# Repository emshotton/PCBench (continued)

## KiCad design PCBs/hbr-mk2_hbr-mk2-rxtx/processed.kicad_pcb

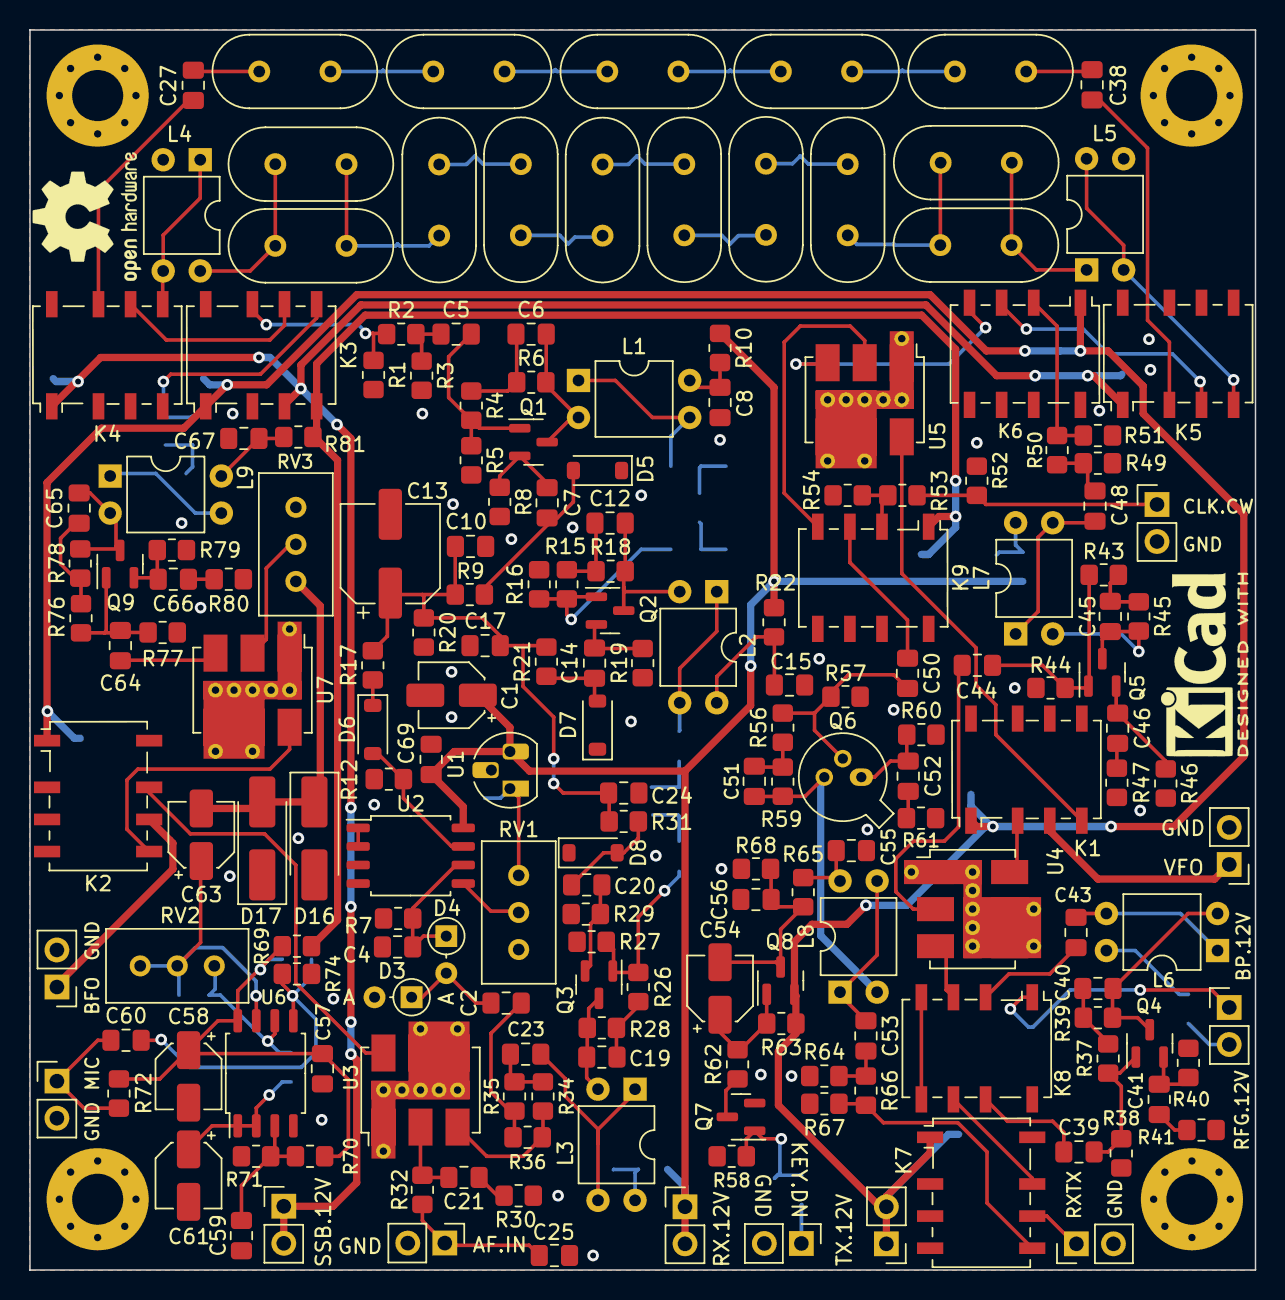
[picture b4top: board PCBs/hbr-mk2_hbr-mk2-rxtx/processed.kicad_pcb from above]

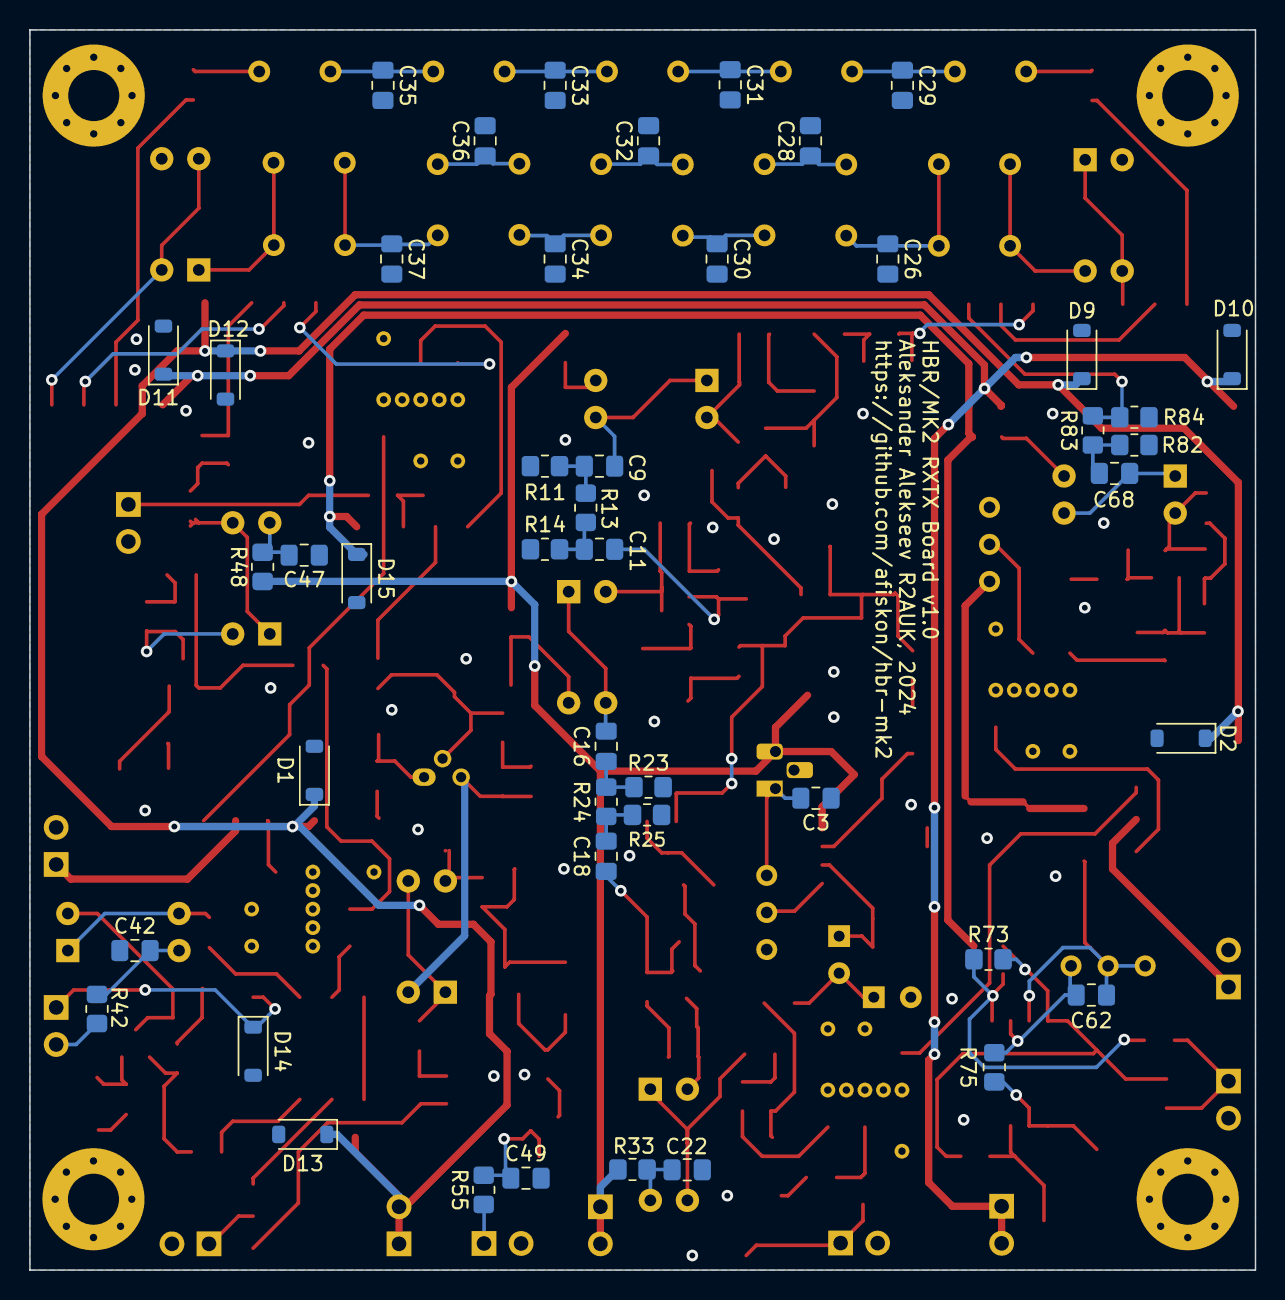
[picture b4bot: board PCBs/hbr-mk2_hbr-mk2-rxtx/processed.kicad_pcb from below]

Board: 2 copper layers, 84.0 x 85.0 mm, 239 parts (46 on the bottom side), 136 nets.

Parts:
C1, C58, C61, C63: 10u; CP_Elec_4x5.4
C2, C3, C5, C6, C7, C8, C9, C10, C11, C12, C14, C15, C16, C17, C18, C19, C20, C22, C23, C24, C39, C40, C41, C42, C43, C44, C45, C46, C47, C48, C49, C50, C51, C52, C53, C55, C56, C57, C59, C60, C64, C65, C66, C67, C68, C69: 0.1u; C_0805_2012Metric_Pad1.18x1.45mm_HandSolder
C4: 820p; C_0805_2012Metric_Pad1.18x1.45mm_HandSolder
C13: 100u; CP_Elec_6.3x7.7
C21: 10n; C_0805_2012Metric_Pad1.18x1.45mm_HandSolder
C25: 47n; C_0805_2012Metric_Pad1.18x1.45mm_HandSolder
C26, C28, C30, C32, C34, C36, C37: 56p; C_0805_2012Metric_Pad1.18x1.45mm_HandSolder
C27, C29, C31, C33, C35, C38: 270p; C_0805_2012Metric_Pad1.18x1.45mm_HandSolder
C54: 2.2u; CP_Elec_4x5.4
C62: 1n; C_0805_2012Metric_Pad1.18x1.45mm_HandSolder
D1, D2, D5, D6, D7, D8, D9, D10, D11, D12, D13, D14, D15: 1N4148W; D_SOD-123
D3, D4: 1N34/D311; D_DO-34_SOD68_P2.54mm_Vertical_AnodeUp
D16, D17: SS14; D_SMA_Handsoldering
H1, H2, H3, H4: MountingHole_Pad; MountingHole_3.5mm_Pad_Via
J1, J2, J3, J4, J5, J6, J7, J8, J9, J10, J11: Conn_01x02; PinHeader_1x02_P2.54mm_Vertical
K1, K2, K3, K4, K5, K6, K7, K8, K9: G6K-2F-Y; Relay_DPDT_Omron_G6K-2F-Y
L1, L2, L3, L4, L5, L6, L7, L8, L9: FT37-43; DIP-4_W7.62mm
Q1, Q2, Q3, Q4, Q5, Q9: MMBT3904; SOT-23
Q6: KT3142A; TO-18-3
Q7: 2N7002; SOT-23
Q8: MMBT3906; SOT-23
R1, R3, R11, R14, R23, R25, R49, R51, R64, R67, R82, R84: 150; R_0805_2012Metric_Pad1.20x1.40mm_HandSolder
R2, R13, R24, R50, R66, R83: 36; R_0805_2012Metric_Pad1.20x1.40mm_HandSolder
R4, R15, R26: 820; R_0805_2012Metric_Pad1.20x1.40mm_HandSolder
R5, R9, R16, R20, R21, R27, R31, R38, R44, R57, R72, R75, R77: 1K; R_0805_2012Metric_Pad1.20x1.40mm_HandSolder
R6, R18, R28, R39, R45, R59, R78: 3.3K; R_0805_2012Metric_Pad1.20x1.40mm_HandSolder
R7, R12, R58, R70, R71, R73, R74: 10K; R_0805_2012Metric_Pad1.20x1.40mm_HandSolder
R8, R19, R29, R40, R46, R60, R79: 68; R_0805_2012Metric_Pad1.20x1.40mm_HandSolder
R10, R22, R33: 100; R_0805_2012Metric_Pad1.20x1.40mm_HandSolder
R17: 220; R_0805_2012Metric_Pad1.20x1.40mm_HandSolder
R30, R34, R35, R36: 51; R_0805_2012Metric_Pad1.20x1.40mm_HandSolder
R32: 1.5K; R_0805_2012Metric_Pad1.20x1.40mm_HandSolder
R37, R43, R56, R76: 1.3K; R_0805_2012Metric_Pad1.20x1.40mm_HandSolder
R41, R47, R61, R80: 6; R_0805_2012Metric_Pad1.20x1.40mm_HandSolder
R42, R48, R55, R65, R69, R81: 22; R_0805_2012Metric_Pad1.20x1.40mm_HandSolder
R52, R53, R54: 82; R_0805_2012Metric_Pad1.20x1.40mm_HandSolder
R62: 2.2K; R_0805_2012Metric_Pad1.20x1.40mm_HandSolder
R63: 680; R_0805_2012Metric_Pad1.20x1.40mm_HandSolder
R68: 1.8K; R_0805_2012Metric_Pad1.20x1.40mm_HandSolder
RV1, RV3: 10K; Potentiometer_Bourns_3296W_Vertical
RV2: 100K; Potentiometer_Bourns_3296W_Vertical
SYM1: Logo_Open_Hardware_Small; OSHW-Logo2_9.8x8mm_SilkScreen
SYM2: SYM_Radio_Waves_Large; KiCad-Logo2_5mm_SilkScreen
U1: L78L33; TO-92_HandSolder
U2: LM358; SOIC-8_5.23x5.23mm_P1.27mm
U3, U4, U5, U7: ADE-6; Mini-Circuits_CD542_LandPatternPL-052
U6: NE5532; SOIC-8_5.23x5.23mm_P1.27mm
Y1, Y2, Y3, Y4, Y5, Y6, Y7, Y8, Y9, Y10, Y11, Y12, Y13, Y14, Y15: 9.000; Crystal_HC49-U_Vertical

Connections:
AGC_DET: C2.1, R35.2, R36.2
AGC_OUT: R34.2, R36.1, U3.3 (RF)
AGC_VC: C10.2, C13.1, C17.2, C24.2, R9.2, R17.2, R20.1, R21.2, R31.2
BFO_RX: K2.7, U3.6 (LO)
BFO_TX: K2.5, U7.6 (LO)
GND: C1.2, C3.1, C4.1, C8.1, C10.1, C13.2, C15.1, C17.1, C22.1, C24.1, C25.1, C26.2, C28.2, C29.2, C30.2, C31.2, C32.2, C33.2, C34.2, C35.2, C36.2, C37.2, C42.1, C47.1, C49.2, C55.2, C56.2, C57.2, C58.2, C59.2, C61.2, C67.1, C69.1, D1.2 (A), D2.2 (A), D3.2 (A), D5.1 (K), D7.1 (K), D8.1 (K), D9.2 (A), D10.2 (A), D11.2 (A), D12.2 (A), D13.2 (A), D14.2 (A), D15.2 (A), D16.2 (A), D17.1 (K), H1.1, H2.1, H3.1, H4.1, J4.2, J5.2, J6.2, J7.2, J9.2, J10.2, J11.2, K1.5, K1.6, K1.7, K1.8, K2.2, K2.3, K2.4, K2.8, K3.8, K4.2, K4.3, K4.4, K4.8, K5.5, K5.6, K5.7, K5.8, K6.5, K6.6, K6.7, K6.8, K7.2, K7.3, K7.4, K7.8, K8.8, K9.5, K9.6, K9.7, K9.8, L4.2, L5.3, Q7.2 (S), R1.2, R3.2, R5.2, R7.2, R8.2, R11.2, R12.2, R14.2, R16.2, R19.2, R20.2, R23.2, R25.2, R27.2, R29.2, R30.2, R38.2, R40.2, R41.2, R44.2, R46.2, R47.2, R49.2, R51.2, R52.2, R54.2, R57.2, R58.2, R60.2, R61.2, R64.2, R67.2, R68.2, R71.2, R74.2, R77.2, R79.2, R80.2, R82.2, R84.2, RV1.3, RV3.3, U1.2 (GND), U2.3 (+), U2.4 (V-), U3.1 (GND), U3.4 (GND), U3.5 (GND), U4.1 (GND), U4.4 (GND), U4.5 (GND), U5.1 (GND), U5.4 (GND), U5.5 (GND), U6.4 (V-), U7.1 (GND), U7.4 (GND), U7.5 (GND)
unnamed: C5.1, R2.2, R3.1
unnamed: C6.1, R4.1, R6.1
unnamed: C8.2, L1.4, R10.2
unnamed: C9.1, L1.1, L1.3
unnamed: C9.2, R11.1, R13.1
unnamed: C11.1, R13.2, R14.1
unnamed: C12.1, R15.1, R18.1
unnamed: C15.2, L2.4, R22.2
unnamed: C16.1, L2.1, L2.3
unnamed: C16.2, R23.1, R24.1
unnamed: C18.1, R24.2, R25.1
unnamed: C19.1, R26.1, R28.1
unnamed: C21.1, R30.1
unnamed: C22.2, L3.4, R33.2
unnamed: C23.1, L3.1, L3.3
unnamed: C23.2, R34.1, R35.1
unnamed: C26.1, Y1.2, Y2.2, Y3.1
unnamed: C27.1, K4.7
unnamed: C27.2, Y4.1
unnamed: C28.1, Y3.2, Y5.1
unnamed: C29.1, Y4.2, Y6.1
unnamed: C30.1, Y5.2, Y7.1
unnamed: C31.1, Y6.2, Y8.2
unnamed: C32.1, Y7.2, Y9.2
unnamed: C33.1, Y8.1, Y10.2
unnamed: C34.1, Y9.1, Y11.2
unnamed: C35.1, Y10.1, Y12.2
unnamed: C36.1, Y11.1, Y13.2
unnamed: C37.1, Y13.1, Y14.2, Y15.2
unnamed: C38.1, Y12.1
unnamed: C38.2, K5.2
unnamed: C39.1, K8.7
unnamed: C40.1, R37.1, R39.1
unnamed: C41.1, R41.1
unnamed: C42.2, L6.4, R42.2
unnamed: C43.1, L6.1, L6.3
unnamed: C43.2, K8.2
unnamed: C45.1, R43.1, R45.1
unnamed: C46.1, R47.1
unnamed: C47.2, L7.4, R48.2
unnamed: C48.1, L7.1, L7.3
unnamed: C48.2, R49.1, R50.1
unnamed: C50.1, K9.3
unnamed: C51.1, R56.1, R59.1
unnamed: C52.1, R61.1
unnamed: C53.1, L8.1, L8.3
unnamed: C53.2, R64.1, R66.1
unnamed: C55.1, L8.4, R65.2
unnamed: C62.2, C63.1, RV2.1, RV2.2, U6.7
unnamed: C65.1, R76.1, R78.1
unnamed: C66.1, R80.1
unnamed: C67.2, L9.4, R81.2
unnamed: C68.1, L9.1, L9.3
unnamed: C68.2, R82.1, R83.1
unnamed: C2.2, D3.1 (K), D4.2 (A)
unnamed: C4.2, D4.1 (K), R7.1, U2.6 (-)
unnamed: C7.1, D5.2 (A), R9.1
unnamed: D6.2 (A), R12.1, U2.7
unnamed: D6.1 (K), R17.1
unnamed: C14.1, D7.2 (A), R21.1
unnamed: C20.1, D8.2 (A), R31.1
unnamed: C63.2, D16.1 (K), D17.2 (A), RV3.1
unnamed: J4.1, K1.3
unnamed: J5.1, K2.6
unnamed: C25.2, J6.1, R32.2
unnamed: J7.1, K7.6
unnamed: J9.1, R52.1, R53.1
unnamed: J10.1, R55.1
unnamed: C60.1, J11.1, R72.2
unnamed: K3.6, K4.6
unnamed: K4.5, L4.1, L4.3
unnamed: K5.3, K6.3
unnamed: K5.4, L5.2, L5.4
unnamed: K7.7, K8.6
unnamed: K9.2, R53.2, R54.1
unnamed: L4.4, Y1.1, Y2.1
unnamed: L5.1, Y14.1, Y15.1
unnamed: C5.2, Q1.1 (B), R4.2, R5.1
unnamed: C6.2, L1.2, Q1.3 (C), R6.2
unnamed: C7.2, Q1.2 (E), R8.1
unnamed: C11.2, Q2.1 (B), R15.2, R16.1
unnamed: C12.2, L2.2, Q2.3 (C), R18.2
unnamed: C14.2, Q2.2 (E), R19.1
unnamed: C18.2, Q3.1 (B), R26.2, R27.1
unnamed: C19.2, L3.2, Q3.3 (C), R28.2
unnamed: C20.2, Q3.2 (E), R29.1
unnamed: C39.2, Q4.1 (B), R37.2, R38.1
unnamed: C40.2, L6.2, Q4.3 (C), R39.2
unnamed: C41.2, Q4.2 (E), R40.1
unnamed: C44.2, Q5.1 (B), R43.2, R44.1
unnamed: C45.2, L7.2, Q5.3 (C), R45.2
unnamed: C46.2, Q5.2 (E), R46.1
unnamed: C50.2, Q6.2 (B), R56.2, R57.1
unnamed: C51.2, L8.2, Q6.3 (C), R59.2
unnamed: C52.2, Q6.1 (E), R60.1
unnamed: Q7.3 (D), R62.1
unnamed: C49.1, Q7.1 (G), R55.2, R58.1
unnamed: C54.1, Q8.1 (B), R62.2, R63.2
unnamed: C54.2, C56.1, Q8.3 (C), R65.1, R68.1
unnamed: C64.2, Q9.1 (B), R76.2, R77.1
unnamed: C65.2, L9.2, Q9.3 (C), R78.2
unnamed: C66.2, Q9.2 (E), R79.1
unnamed: C3.2, RV1.1, U1.1 (VO)
unnamed: U2.1, U2.2 (-)
unnamed: RV1.2, U2.5 (+)
unnamed: C21.2, R32.1, U3.2 (IF)
unnamed: C44.1, U4.2 (IF)
unnamed: K8.3, U4.3 (RF)
unnamed: K9.4, U5.2 (IF)
unnamed: C59.1, R70.2, R71.1, U6.3 (+)
unnamed: C61.1, R75.2, U6.1, U6.2 (-)
unnamed: C60.2, R73.2, R74.1, U6.5 (+)
unnamed: C62.1, R75.1, RV2.3, U6.6 (-)
unnamed: C57.1, C58.1, R69.2, R70.1, R72.1, R73.1, U6.8 (V+)
unnamed: RV3.2, U7.2 (IF)
unnamed: C64.1, U7.3 (RF)
RF_AMP_12V: J8.2, R42.1
RF_AMP_BYPASS: K8.4, K8.5
RF_AMP_BYPASS_12V: D14.1 (K), J8.1, K8.1
RX_12V: C1.1, C69.2, J1.1, J1.2, R10.1, R22.1, R33.1, R48.1, U1.3 (VI), U2.8 (V+)
SSB_12V: D10.1 (K), D11.1 (K), J3.1, J3.2, K3.3, K4.1, K5.1
SSB_TX_12V: D15.1 (K), K3.4, K9.1, R69.1, R81.1
TX_12V: D1.1 (K), D2.1 (K), D9.1 (K), D12.1 (K), D13.1 (K), J2.1, J2.2, K1.1, K2.1, K3.1, K6.1, K7.1, Q8.2 (E), R63.1
TX_COMMON_OUT: K7.5, R66.2, R67.1
VFO_RX: K1.2, U4.6 (LO)
VFO_TX: K1.4, U5.6 (LO)
XFLT_RX_IN: K6.2, R50.2, R51.1
XFLT_RX_OUT: K3.7, R1.1, R2.1
XFLT_TX_IN: K3.5, R83.2, R84.1
XFLT_TX_OUT: K6.4, U5.3 (RF)

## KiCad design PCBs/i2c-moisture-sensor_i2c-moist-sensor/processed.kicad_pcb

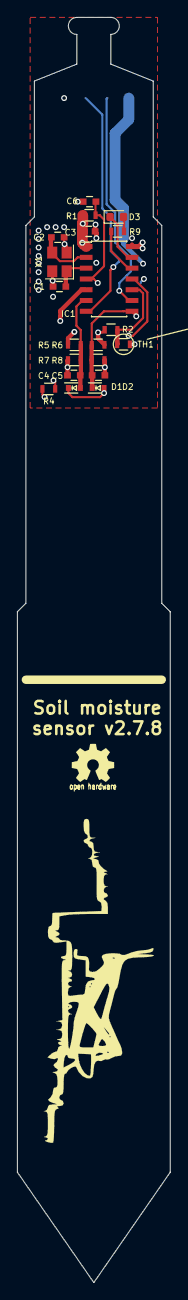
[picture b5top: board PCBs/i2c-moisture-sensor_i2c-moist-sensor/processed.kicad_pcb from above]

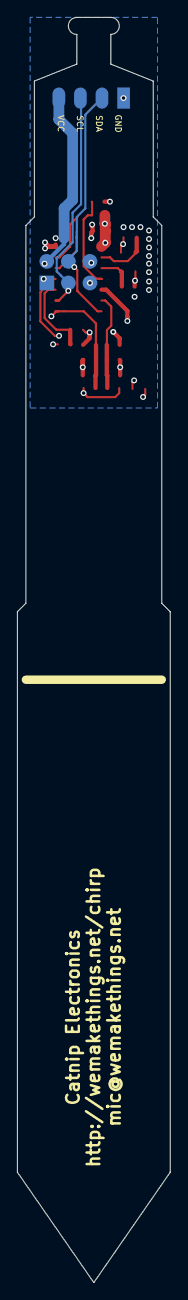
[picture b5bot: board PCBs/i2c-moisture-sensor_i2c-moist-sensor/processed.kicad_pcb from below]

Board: 4 copper layers, 18.0 x 149.0 mm, 22 parts (2 on the bottom side), 16 nets.

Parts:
C1: 33p; C_0603
C2: 33pp; C_0603
C3, C6: 1u; C_0603
C4, C5: 1n; C_0603
D1, D2: BAT54; SOD-523
D3: LED; LED_0603_1608Metric
IC1: ATTINY441-SSU; SOIC-14_3.9x8.7mm_Pitch1.27mm
P1: CONN_02X03; Pin_Header_Straight_2x03
P2: CONN_01X04; Pin_Header_Straight_1x04_Pitch2.54mm
R1: 10k; R_0603
R2: 10k 0.1%; R_0603
R4, R9: 330; R_0603
R5, R6, R7, R8: 1M; R_0603
TH1: NCP18XH103F03RB; R_0603
X1: 16MHz; Crystal_SMD_3225-4pin_3.2x2.5mm

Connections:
/EXCITATION: IC1.5, R4.2
/MISO/SENSE_HIGH: C5.1, D2.2, IC1.8, P1.1, R6.1, R8.2
/MOSI/SDA: IC1.7, P1.4, P2.2
/RESET: C6.1, IC1.4, P1.5, R1.1
/SCK/SCL: IC1.9, P1.3, P2.3
/SENSE_LOW: C4.1, D1.1, IC1.6, R5.1, R7.2
/SENSOR_TRACK: D1.2, D2.1, R4.1
/THERMISTOR: IC1.10, R2.2, TH1.1
GND: C1.2, C2.2, C3.2, C4.2, C5.2, C6.2, IC1.14, P1.6, P2.1, R7.1, R8.1, TH1.2, X1.2, X1.4
unnamed: C1.1, IC1.3, X1.1
unnamed: C2.1, IC1.2, X1.3
unnamed: D3.1, IC1.13
unnamed: D3.2, R9.1
unnamed: IC1.11, R2.1, R5.2, R6.2
unnamed: IC1.12, R9.2
VCC: C3.1, IC1.1, P1.2, P2.4, R1.2

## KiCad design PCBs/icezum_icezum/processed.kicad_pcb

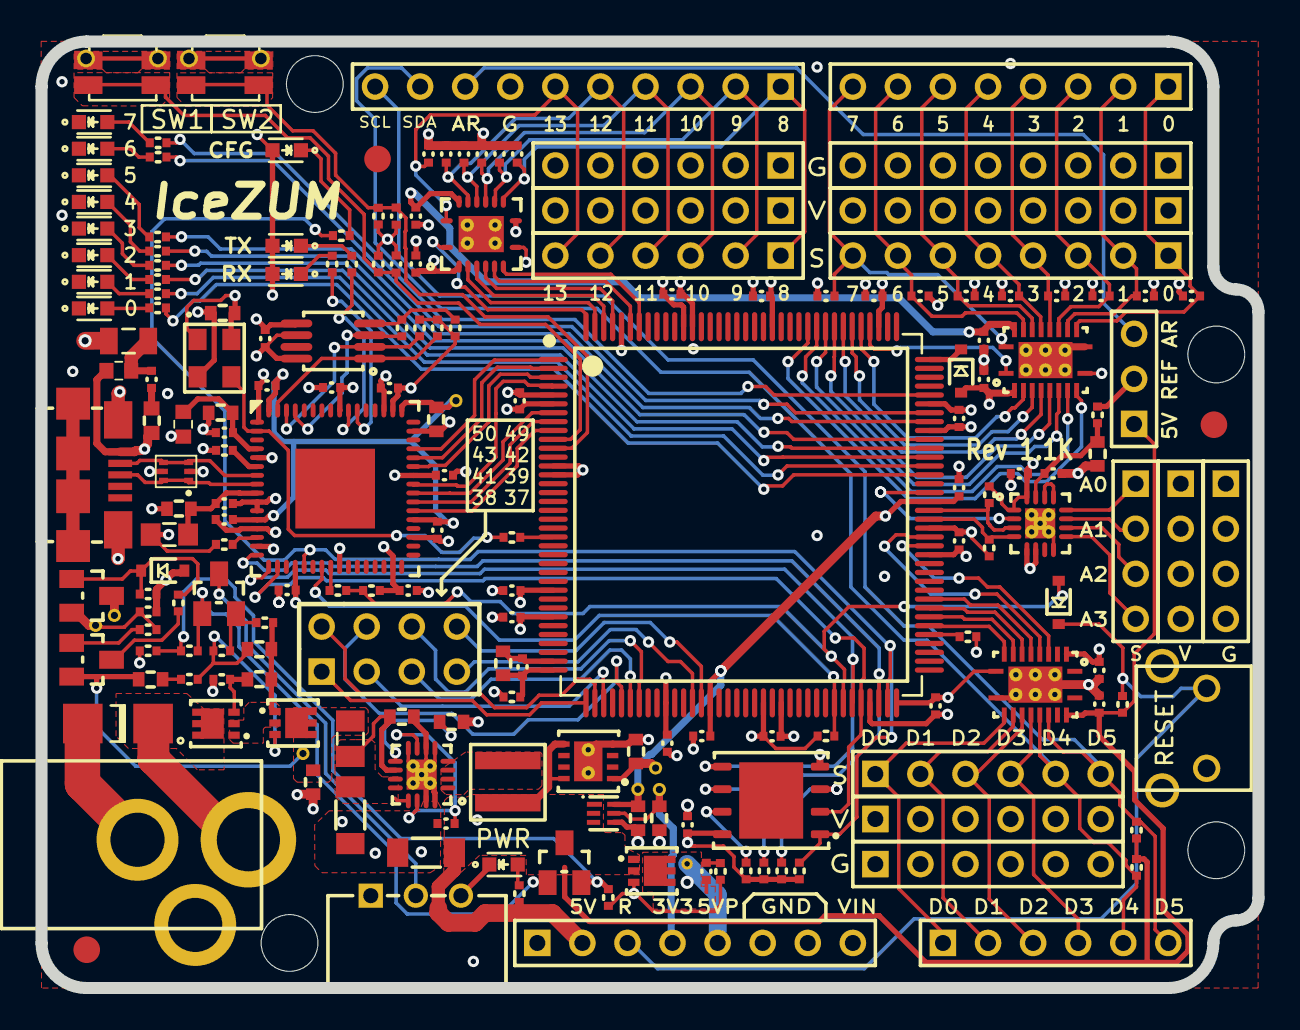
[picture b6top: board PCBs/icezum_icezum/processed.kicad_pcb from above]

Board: 4 copper layers, 68.6 x 53.3 mm, 211 parts (0 on the bottom side), 144 nets.

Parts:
C1, C2, C3, C4, C5, C6, C7, C8, C9, C10, C12, C13, C14, C15, C16, C18, C19, C20, C21, C23, C25, C26, C27, C28, C29, C30, C33, C34, C35, C36, C37, C45, C46, C47, C48, C49, C50, C63, C68: 100nF; C_0402
C11: 10uF; C_0603
C17, C24, C31, C41, C59, C64, C65: 4.7uF; C_0603
C22, C32, C60, C61: 10nF; C_0603
C38, C39, C40, C42, C43, C44, C51, C52, C53, C54, C55, C56, C57, C58: 100pF; C_0402
C62, C66, C70: 100nF; C_0603
C67: 10uF; C_1206
C69: 22uF; C_1206
C71: 620pF; C_0603
D1, D4: NSR0530HT1G; SOD-323
D2: BZX384C5V1-E3; SOD-323
D10: SMAJ17CA; DO-214AC
D11: BAT54C-G3-08; SOT-23
D12: White; LED_0603
DOC1, DOC3: icezum-headers-doc; None
DOC4, DOC5: switch_DOC; None
F1: 0,5A; F_0805
F2: ESDUSB; SOT-563
FID1, FID2, FID3: FIDUCIAL; Fiducial
J1: USB_Micro_Type_B; USB_Micro-B
J2, J3, J6, J12, J13, J14: 1x6_male_pin_Header_2.54mm; 1x6-pin-header-2.54mm
J4: 1x10_female_pin_Header_2.54mm; 1x10_socket-header-2.54mm
J5, J10: 1x8_female_pin_Header_2.54mm; 1x8_Socket_header_2.54mm
J7, J8, J9: 1x8_male_pin_Header_2.54mm; 1x8_pin_header_2.54mm
J11: 1x6_female_pin_Header_2.54mm; 1x6-Socket-header-2.54mm
J15, J16, J17: 1x4_male_pin_Header_2.54mm; 1x04-pin-header-2.54mm
J18: Power_Jack; JACK_2.1
J19: 2x4_male_pin_Header_2.54mm; 2x04-pin-header-2.54mm
JP1: Jumper_3pin; 1x03-pin-header-2.54mm
JPM1: Jumper_1x2_Mech; None
L1: 10uH 0,1A; L_0805
L2, L3: BLM18SG121TN1D; L_0603
L4: Ferrite_Bead; L_0806
L5: 2,2uH 4,7A; L_4040
LD0, LD1, LD2, LD3, LD4, LD5, LD6, LD7, LD8: Green; LED_0603
LD9, LD10: Yellow; LED_0603
Q1, Q2, Q4: DMP3017; DFN-2523-6
Q3: DMP2035U-7; SOT-23
Q5: PMBT3906; SOT-23
R1, R3, R4, R5, R6, R7, R8, R12, R13, R14, R20, R21, R24, R25, R27, R28, R30, R33, R34, R37, R38: 10k±5% 0.063w; R_0402
R2: 470R±5% 0.063w; R_0402
R9, R35: 100R±5% 0.063w; R_0402
R10, R15, R17, R18, R40, R41, R42, R43, R44, R45, R46, R47, R48: 2k2±5% 0.063w; R_0402
R11: 12k±1% 0.063w; R_0402
R16: 0R±5% 0.063w; R_0402
R19: 10R±5% 0.063w; R_0402
R22, R23: 4K7±5% 0.063w; R_0402
R26, R29, R36: 100k±5% 0.063w; R_0402
R31, R32: 10k±5% 0.0625w; R_0402
R39: 2k2k±5% 0.063w; R_0402
SW1, SW2: Switch_4p; WE_434331013822
SW3: SPDT_Switch; slide-sw-spdt-right-angle
SW4: Switch; SW_vert_tht_7.5x6x6.5
TP1, TP2, TP3, TP4, TP5, TP6, TP7, TP8: TestPoint_Small; Via_Test_point
U1: iCE40HX1K-TQ144; TQFP-144_IPC-MD
U2: N25Q032A; DFN-8-6x5mm
U3: FT2232H; FTDI-QFN-64
U4: DSC1001; Xtal-3_2x2_5
U5: 93LC56C; MSOP-8_3x3mm_Pitch0.65mm
U6: TXB0106; VQFN16_VIATP
U7: ADS7924; QFN16_VIATP
U8: TXS0108; VQFN20_VIATP
U9: TXB0108; VQFN20_VIATP
U10: AP7361; DFN-3030-8_VIATP
U11: TLV711; WSON-6
U12: TPS62133RGTR; QFN16_VIATP
U13: APX810; SOT-23
doc1, doc6: 1x8_pin_female_header_DOC; None
doc2: 3x8_pin_male_header_DOC; None
doc3: 1x10_pin_female_header_DOC; None
doc4, doc7: 3x6_pin_male_header_DOC; None
doc5: 2x4_pin_male_header_DOC; None
doc8: 1x6_pin_female_header_DOC; None
doc9: 3x4_pin_male_header_DOC; None
doc10: 1x3_pin_male_header_v_DOC; None

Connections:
+1V2: C13.1, C14.1, C15.1, C16.1, C64.1, R9.2, TP3.1, U1.27, U1.51, U1.92, U1.111, U11.6
+1V8_FT: C19.1, C20.1, C21.1, C31.1, TP8.1, U3.12, U3.37, U3.49, U3.64
+3V3: C1.1, C2.1, C3.1, C4.1, C5.1, C6.1, C7.1, C8.1, C9.1, C10.1, C26.1, C27.1, C28.1, C29.1, C30.1, C32.1, C33.1, C36.2, C45.1, C47.2, C49.2, C59.1, D1.2, L1.1, L3.1, LD8.A, LD9.A, LD10.A, R1.2, R3.2, R5.1, R6.1, R7.1, R8.1, R10.1, R12.1, R13.1, R14.1, R20.2, R21.2, SW1.3, SW1.4, SW2.3, SW2.4, TP2.1, U1.6, U1.30, U1.46, U1.57, U1.72, U1.89, U1.100, U1.123, U1.133, U2.8, U3.20, U3.31, U3.42, U3.50, U3.56, U4.1, U4.4, U5.6, U5.8, U6.2, U6.8, U7.1, U7.16, U8.2, U8.10, U9.2, U9.10, U10.1
+3V3_AUX: C65.1, J5.4, TP4.1, U11.5
+5V: C37.1, C48.1, C50.1, C68.1, C69.1, J5.2, JP1.1, L5.2, Q3.3, Q4.1, Q4.2, R22.2, R23.2, R30.1, R34.1, R36.2, TP1.1, U6.15, U8.19, U9.19, U10.5, U10.8, U11.1, U11.2, U11.3, U12.7, U12.14, U13.3
+5V_P: C63.1, J2.1, J2.2, J2.3, J2.4, J2.5, J2.6, J5.5, J7.1, J7.2, J7.3, J7.4, J7.5, J7.6, J7.7, J7.8, J13.1, J13.2, J13.3, J13.4, J13.5, J13.6, J15.1, J15.2, J15.3, J15.4, Q4.4, Q4.5, Q4.6, TP5.1
/Arduino sockets/D0: C54.1, J9.1, J10.1, U9.12
/Arduino sockets/D1: C55.1, J9.2, J10.2, U9.13
/Arduino sockets/D2: C51.1, J9.3, J10.3, U9.14
/Arduino sockets/D3: C56.1, J9.4, J10.4, U9.15
/Arduino sockets/D4: C52.1, J9.5, J10.5, U9.16
/Arduino sockets/D5: C57.1, J9.6, J10.6, U9.17
/Arduino sockets/D6: C53.1, J9.7, J10.7, U9.18
/Arduino sockets/D7: C58.1, J9.8, J10.8, U9.20
/Arduino sockets/D8: C40.1, J4.1, J6.1, U6.10
/Arduino sockets/D9: C42.1, J4.2, J6.2, U6.11
/Arduino sockets/D10: C38.1, J4.3, J6.3, U6.12
/Arduino sockets/D11: C43.1, J4.4, J6.4, U6.13
/Arduino sockets/D12: C39.1, J4.5, J6.5, U6.14
/Arduino sockets/D13: C44.1, J4.6, J6.6, U6.16
/Arduino sockets/DD0: J11.1, J12.1, U8.12
/Arduino sockets/DD1: J11.2, J12.2, U8.13
/Arduino sockets/DD2: J11.3, J12.3, U8.14
/Arduino sockets/DD3: J11.4, J12.4, U8.15
/Arduino sockets/DD4: J4.9, J11.5, J12.5, R23.1, U8.16
/Arduino sockets/DD5: J4.10, J11.6, J12.6, R22.1, U8.17
/Peripherals/A0: J17.1, U7.12
/Peripherals/A1: J17.2, U7.11
/Peripherals/A2: J17.3, U7.10
/Peripherals/A3: J17.4, U7.9
/Power Supply/5V_P_CTL: D11.1, R37.1, U13.1
/USB communications/FT_CLK: R13.2, U3.62, U5.2
/USB communications/FT_CS: R12.2, U3.63, U5.1
/USB communications/FT_DATA: R15.1, U3.61, U5.3
/USB communications/USB_N: F2.3, F2.4, J1.2, U3.7
/USB communications/USB_P: F2.1, F2.6, J1.3, U3.8
ADC_INT: U1.93, U7.2
ADC_SCL: R20.1, U1.91, U7.3
ADC_SDA: R21.1, U1.90, U7.4
AREF: J4.8, JP1.3
FPGA_37: J19.1, U1.37
FPGA_38: J19.2, U1.38
FPGA_39: J19.3, U1.39
FPGA_41: J19.4, U1.41
FPGA_42: J19.5, U1.42
FPGA_43: J19.6, U1.43
FPGA_49_GBIN5: J19.7, U1.49
FPGA_50_GBIN4: J19.8, U1.50
FPGA_78: U1.78, U8.9
FPGA_79: U1.79, U8.8
FPGA_80: U1.80, U8.7
FPGA_81: U1.81, U8.6
FPGA_87: U1.87, U8.4
FPGA_88: U1.88, U8.5
FPGA_112: U1.112, U9.1
FPGA_113: U1.113, U9.3
FPGA_114: U1.114, U9.4
FPGA_115: U1.115, U9.5
FPGA_116: U1.116, U9.6
FPGA_117: U1.117, U9.7
FPGA_118: U1.118, U9.8
FPGA_119: U1.119, U9.9
FPGA_138: U1.138, U6.7
FPGA_139: U1.139, U6.6
FPGA_141: U1.141, U6.5
FPGA_142: U1.142, U6.4
FPGA_143: U1.143, U6.3
FPGA_144: U1.144, U6.1
FPGA_RESET: D4.2, R2.1, R3.1, U1.66
FT_CTS: U1.4, U3.41
FT_DCD: U1.1, U3.45
FT_DSR: U1.2, U3.44
FT_DTR: U1.3, U3.43
FT_RTS: U1.7, U3.40
FT_RX: U1.8, U3.39
FT_TX: U1.9, U3.38
GNDREF: C1.2, C2.2, C3.2, C4.2, C5.2, C6.2, C7.2, C8.2, C9.2, C10.2, C13.2, C14.2, C15.2, C16.2, C17.2, C18.2, C19.2, C20.2, C21.2, C22.2, C23.2, C24.2, C25.2, C26.2, C27.2, C28.2, C29.2, C30.2, C31.2, C32.2, C33.2, C34.1, C35.1, C36.1, C37.2, C38.2, C39.2, C40.2, C41.1, C42.2, C43.2, C44.2, C45.2, C46.1, C47.1, C48.2, C49.1, C50.2, C51.2, C52.2, C53.2, C54.2, C55.2, C56.2, C57.2, C58.2, C59.2, C64.2, C65.2, C66.2, C67.2, C68.2, C69.2, C70.2, C71.2, D2.2, D10.A, D12.K, F2.2, J1.4, J1.5, J1.S1, J1.S2, J1.S3, J1.S4, J1.S5, J1.S6, J3.1, J3.2, J3.3, J3.4, J3.5, J3.6, J4.7, J5.6, J5.7, J8.1, J8.2, J8.3, J8.4, J8.5, J8.6, J8.7, J8.8, J14.1, J14.2, J14.3, J14.4, J14.5, J14.6, J16.1, J16.2, J16.3, J16.4, J18.3, LD0.K, LD1.K, LD2.K, LD3.K, LD4.K, LD5.K, LD6.K, LD7.K, R4.2, R11.1, R25.1, R29.1, R31.1, R32.1, R39.1, SW3.3, SW4.2, U1.5, U1.13, U1.14, U1.59, U1.69, U1.86, U1.103, U1.132, U1.140, U2.4, U3.1, U3.5, U3.10, U3.11, U3.13, U3.15, U3.25, U3.35, U3.47, U3.51, U4.2, U5.5, U6.9, U6.17, U7.5, U7.6, U7.8, U7.17, U8.11, U8.21, U9.11, U9.21, U10.4, U10.9, U11.4, U12.5, U12.6, U12.8, U12.15, U12.16, U12.17
LED0: R17.2, U1.95
LED1: R18.2, U1.96
LED2: R40.2, U1.97
LED3: R41.2, U1.98
LED4: R42.2, U1.99
LED5: R43.2, U1.101
LED6: R44.2, U1.102
LED7: R45.2, U1.104
unnamed: C11.1, C12.1, R9.1, U1.36
unnamed: C11.2, C12.2, U1.35
unnamed: C17.1, C18.1, L1.2, U3.9
unnamed: C22.1, F2.5, J1.1, L2.1
unnamed: C23.1, F1.1, L2.2
unnamed: C24.1, C25.1, L3.2, U3.4
unnamed: C41.2, C46.2, R19.1, U7.15
unnamed: C60.2, R24.2
unnamed: C61.1, C62.2, Q1.1, Q1.2, Q2.1, Q2.2, R26.2
unnamed: C61.2, Q1.3, R25.2
unnamed: C62.1, Q2.3, R24.1, R27.2
unnamed: C63.2, R35.2
unnamed: C67.1, C70.1, L4.2, U12.10, U12.11, U12.12, U12.13
unnamed: C71.1, U12.9
unnamed: D1.1, U1.108
unnamed: D2.1, Q3.1, R28.2, R29.2
unnamed: D11.2, R26.1, R27.1
unnamed: D11.3, SW3.2
unnamed: D12.A, R34.2
unnamed: JP1.2, R19.2
unnamed: L5.1, U12.1, U12.2, U12.3
unnamed: LD0.A, R17.1
unnamed: LD1.A, R18.1
unnamed: LD2.A, R40.1
unnamed: LD3.A, R41.1
unnamed: LD4.A, R42.1
unnamed: LD5.A, R43.1
unnamed: LD6.A, R44.1
unnamed: LD7.A, R45.1
unnamed: LD8.K, R47.1
unnamed: LD9.K, R48.1
unnamed: LD10.K, R46.2
unnamed: Q4.3, R33.2, R35.1
unnamed: Q5.1, R38.1
unnamed: Q5.3, R28.1
unnamed: R4.1, U1.77
unnamed: R7.2, U2.7
unnamed: R8.2, U2.3
unnamed: R10.2, U3.14
unnamed: R11.2, U3.6
unnamed: R14.2, R15.2, U5.4
unnamed: R16.1, U3.2, U4.3
unnamed: R33.1, R36.1, R37.2, U13.2
unnamed: R47.2, U3.54
unnamed: R48.2, U3.55
unnamed: U7.13, U7.14
Power: C60.1, C66.1, L4.1, Q2.4, Q2.5, Q2.6, Q5.2, TP6.1
SYS_RESET: D4.1, J5.3, R30.2, SW4.1
USB_5V: F1.2, Q3.2, R38.2, R39.2, TP7.1
U_SW1: C34.2, R31.2, SW1.1, SW1.2, U1.10
U_SW2: C35.2, R32.2, SW2.1, SW2.2, U1.11
VIN: D10.K, J5.8, J18.1, Q1.4, Q1.5, Q1.6
iCE_CDONE: R1.1, U1.65, U3.23
iCE_CLK: R16.2, U1.21
iCE_CREST: R2.2, U3.24
iCE_MISO: U1.68, U2.2, U3.18
iCE_MOSI: U1.67, U2.5, U3.17
iCE_SCK: R5.2, U1.70, U2.6, U3.16
iCE_SS_B: R6.2, R46.1, U1.71, U2.1, U3.21

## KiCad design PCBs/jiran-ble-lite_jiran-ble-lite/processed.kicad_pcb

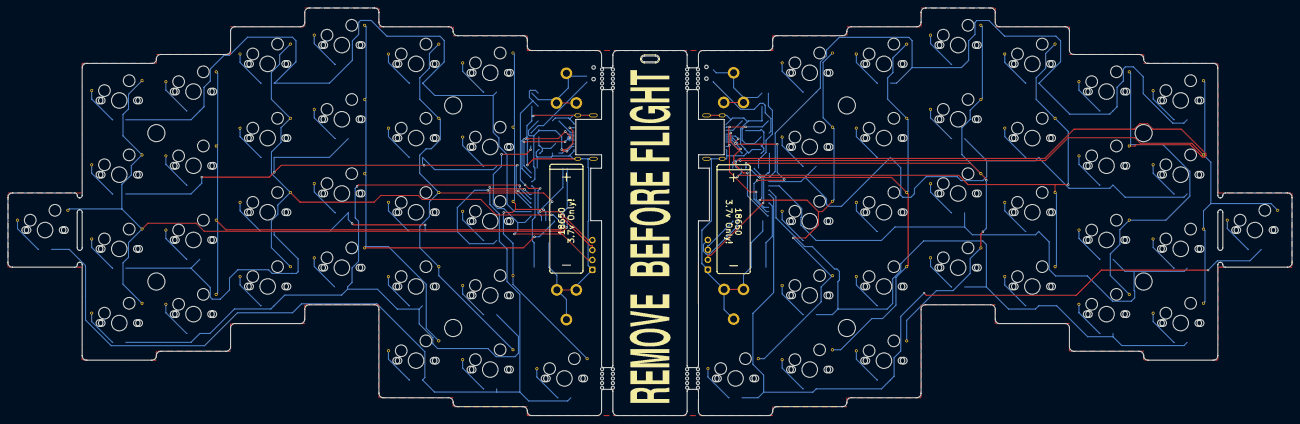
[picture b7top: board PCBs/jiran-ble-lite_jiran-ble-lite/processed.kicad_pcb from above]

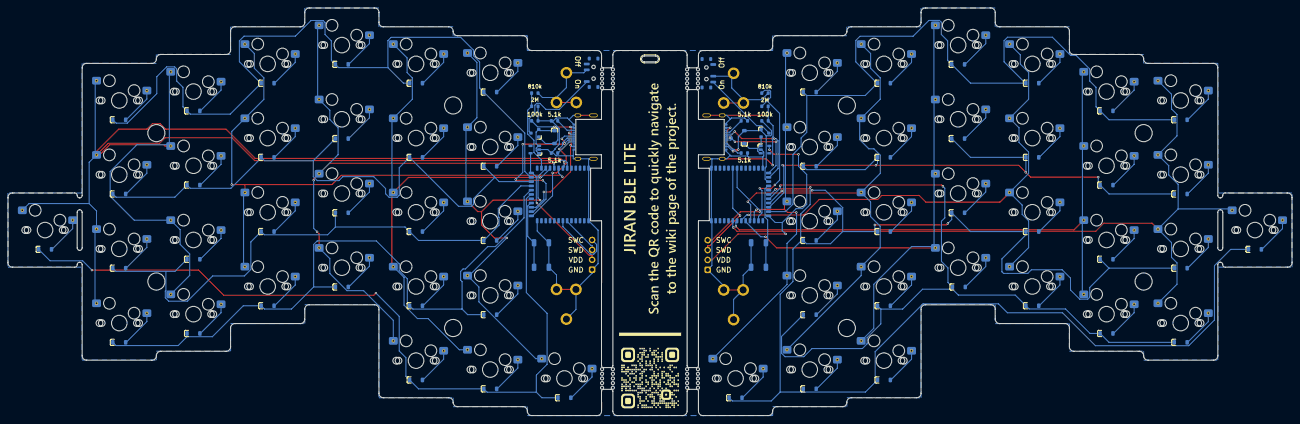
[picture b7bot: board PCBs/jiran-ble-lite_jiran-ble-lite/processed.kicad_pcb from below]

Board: 2 copper layers, 329.7 x 104.6 mm, 154 parts (81 on the bottom side), 105 nets.

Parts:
D1, D2, D3, D4, D5, D6, D7, D8, D9, D10, D11, D12, D13, D14, D15, D16, D17, D18, D19, D20, D21, D22, D23, D24, D25, D26, D27, D28, D29, D30, D31, D32, D33, D34, D35, D36, D37, D38, D39, D40, D41, D42, D43, D44, D45, D46, D47, D48, D49, D50, D51, D52, D53, D54, D55, D56, D57, D58: 1N5819; D_SOD-123
G1: Logo-Jiran-BLE; silk_front
G2: Logo-Jiran-BLE; silk_back
HM1, HM2, HM3, HM4, HM6, HM7, HM8, HM9: CaseHole; Hole_Mount_M4
J1, J4: USB_C_Receptacle_USB2.0; USB-C-C168688
J2, J5: SWD; Connector_THT_1x4_2.54
J3, J6: BATT; Battery_Holder_18650_Nickel
P1, P2, P3, P4: Breakoff; Panel_2x5
Q1, Q2: AO3407; SOT-23
R1, R6: 810k; R_0603
R2, R7: 2M; R_0603
R3, R8: 100k; R_0603
R4, R5, R9, R10: 5.1k; R_0603
SW1, SW2, SW3, SW4, SW5, SW6, SW7, SW8, SW9, SW10, SW11, SW12, SW13, SW14, SW15, SW16, SW17, SW18, SW19, SW20, SW21, SW22, SW23, SW24, SW25, SW26, SW27, SW28, SW30, SW31, SW32, SW33, SW34, SW35, SW36, SW37, SW38, SW39, SW40, SW41, SW42, SW43, SW44, SW45, SW46, SW47, SW48, SW49, SW50, SW51, SW52, SW53, SW54, SW55, SW56, SW57: SW_Push; Switch_Mx_Hotswap_1u
SW29, SW58: SW_DPDT; MSK-12C02
SWT1, SWT2: SW_Push; K2-1187SQ
U1, U3: HOLYIOT-18010-NRF52840_Simple; Holyiot-18010-nRF52840
U2, U4: AP2112K-3.3; SOT-23-5

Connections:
/BT_PIN: R1.2, R2.1, U1.12 (P0.04/AIN2)
/CC1: J1.A5 (CC1), R4.1
/CC2: J1.B5 (CC2), R5.1
/DATA+: J1.A6 (D+), J1.B6 (D+), U1.24 (USB_D+)
/DATA-: J1.A7 (D-), J1.B7 (D-), U1.23 (USB_D-)
/P0.02: SW2.2, SW8.2, SW14.2, SW20.2, U1.7 (P0.02/AIN0)
/P0.03: SW1.2, SW7.2, SW13.2, SW19.2, SW25.2, U1.6 (P0.03/AIN1)
/P0.07: D1.1 (K), D2.1 (K), D3.1 (K), D4.1 (K), D5.1 (K), D6.1 (K), U1.15 (P0.07)
/P0.12: D13.1 (K), D14.1 (K), D15.1 (K), D16.1 (K), D17.1 (K), D18.1 (K), U1.17 (P0.12)
/P0.21: D25.1 (K), D26.1 (K), D27.1 (K), D28.1 (K), U1.19 (P0.21)
/P0.23: D19.1 (K), D20.1 (K), D21.1 (K), D22.1 (K), D23.1 (K), D24.1 (K), U1.18 (P0.23)
/P0.28: SW3.2, SW9.2, SW15.2, SW21.2, U1.8 (P0.28/AIN4)
/P0.29: SW4.2, SW10.2, SW16.2, SW22.2, SW26.2, U1.9 (P0.29/AIN5)
/P0.30: SW5.2, SW11.2, SW17.2, SW23.2, SW27.2, U1.10 (P0.30/AIN6)
/P0.31: SW6.2, SW12.2, SW18.2, SW24.2, SW28.2, U1.11 (P0.31/AIN7)
/P1.09: D7.1 (K), D8.1 (K), D9.1 (K), D10.1 (K), D11.1 (K), D12.1 (K), U1.16 (P1.09)
/RESET: SWT1.1, U1.21 (P0.18/RESET)
/SWC: J2.4, U1.31 (SWDCLK)
/SWD: J2.3, U1.32 (SWDIO)
/VBAT: J3.1, R1.1, SW29.2 (B)
/VBUS: D29.2 (A), J1.A4 (VBUS), Q1.1 (G), R3.1, U1.22 (VBUS)
/jiran-ble-lite-right/BT_PIN: R6.2, R7.1, U3.12 (P0.04/AIN2)
/jiran-ble-lite-right/CC1: J4.A5 (CC1), R9.1
/jiran-ble-lite-right/CC2: J4.B5 (CC2), R10.1
/jiran-ble-lite-right/DATA+: J4.A6 (D+), J4.B6 (D+), U3.24 (USB_D+)
/jiran-ble-lite-right/DATA-: J4.A7 (D-), J4.B7 (D-), U3.23 (USB_D-)
/jiran-ble-lite-right/P0.02: SW31.2, SW37.2, SW43.2, SW49.2, U3.7 (P0.02/AIN0)
/jiran-ble-lite-right/P0.03: SW30.2, SW36.2, SW42.2, SW48.2, SW54.2, U3.6 (P0.03/AIN1)
/jiran-ble-lite-right/P0.07: D30.1 (K), D31.1 (K), D32.1 (K), D33.1 (K), D34.1 (K), D35.1 (K), U3.15 (P0.07)
/jiran-ble-lite-right/P0.12: D42.1 (K), D43.1 (K), D44.1 (K), D45.1 (K), D46.1 (K), D47.1 (K), U3.17 (P0.12)
/jiran-ble-lite-right/P0.21: D54.1 (K), D55.1 (K), D56.1 (K), D57.1 (K), U3.19 (P0.21)
/jiran-ble-lite-right/P0.23: D48.1 (K), D49.1 (K), D50.1 (K), D51.1 (K), D52.1 (K), D53.1 (K), U3.18 (P0.23)
/jiran-ble-lite-right/P0.28: SW32.2, SW38.2, SW44.2, SW50.2, U3.8 (P0.28/AIN4)
/jiran-ble-lite-right/P0.29: SW33.2, SW39.2, SW45.2, SW51.2, SW55.2, U3.9 (P0.29/AIN5)
/jiran-ble-lite-right/P0.30: SW34.2, SW40.2, SW46.2, SW52.2, SW56.2, U3.10 (P0.30/AIN6)
/jiran-ble-lite-right/P0.31: SW35.2, SW41.2, SW47.2, SW53.2, SW57.2, U3.11 (P0.31/AIN7)
/jiran-ble-lite-right/P1.09: D36.1 (K), D37.1 (K), D38.1 (K), D39.1 (K), D40.1 (K), D41.1 (K), U3.16 (P1.09)
/jiran-ble-lite-right/RESET: SWT2.1, U3.21 (P0.18/RESET)
/jiran-ble-lite-right/SWC: J5.4, U3.31 (SWDCLK)
/jiran-ble-lite-right/SWD: J5.3, U3.32 (SWDIO)
/jiran-ble-lite-right/VBAT: J6.1, R6.1, SW58.2 (B)
/jiran-ble-lite-right/VBUS: D58.2 (A), J4.A4 (VBUS), Q2.1 (G), R8.1, U3.22 (VBUS)
/jiran-ble-lite-right/nRF_VDD: J5.2, U3.14 (VDD), U4.5 (VOUT)
/nRF_VDD: J2.2, U1.14 (VDD), U2.5 (VOUT)
GND: J1.A1 (GND), J1.S1 (SHIELD), J2.1, J3.2, J4.A1 (GND), J4.S1 (SHIELD), J5.1, J6.2, R2.2, R3.2, R4.2, R5.2, R7.2, R8.2, R9.2, R10.2, SWT1.2, SWT2.2, U1.1 (GND), U1.25 (GND), U1.37 (GND), U2.2 (GND), U3.1 (GND), U3.25 (GND), U3.37 (GND), U4.2 (GND)
unnamed: D1.2 (A), SW1.1
unnamed: D2.2 (A), SW2.1
unnamed: D3.2 (A), SW3.1
unnamed: D4.2 (A), SW4.1
unnamed: D5.2 (A), SW5.1
unnamed: D6.2 (A), SW6.1
unnamed: D7.2 (A), SW7.1
unnamed: D8.2 (A), SW8.1
unnamed: D9.2 (A), SW9.1
unnamed: D10.2 (A), SW10.1
unnamed: D11.2 (A), SW11.1
unnamed: D12.2 (A), SW12.1
unnamed: D13.2 (A), SW13.1
unnamed: D14.2 (A), SW14.1
unnamed: D15.2 (A), SW15.1
unnamed: D16.2 (A), SW16.1
unnamed: D17.2 (A), SW17.1
unnamed: D18.2 (A), SW18.1
unnamed: D19.2 (A), SW19.1
unnamed: D20.2 (A), SW20.1
unnamed: D21.2 (A), SW21.1
unnamed: D22.2 (A), SW22.1
unnamed: D23.2 (A), SW23.1
unnamed: D24.2 (A), SW24.1
unnamed: D25.2 (A), SW25.1
unnamed: D26.2 (A), SW26.1
unnamed: D27.2 (A), SW27.1
unnamed: D28.2 (A), SW28.1
unnamed: D29.1 (K), Q1.2 (S), U2.1 (VIN), U2.3 (EN)
unnamed: D30.2 (A), SW30.1
unnamed: D31.2 (A), SW31.1
unnamed: D32.2 (A), SW32.1
unnamed: D33.2 (A), SW33.1
unnamed: D34.2 (A), SW34.1
unnamed: D35.2 (A), SW35.1
unnamed: D36.2 (A), SW36.1
unnamed: D37.2 (A), SW37.1
unnamed: D38.2 (A), SW38.1
unnamed: D39.2 (A), SW39.1
unnamed: D40.2 (A), SW40.1
unnamed: D41.2 (A), SW41.1
unnamed: D42.2 (A), SW42.1
unnamed: D43.2 (A), SW43.1
unnamed: D44.2 (A), SW44.1
unnamed: D45.2 (A), SW45.1
unnamed: D46.2 (A), SW46.1
unnamed: D47.2 (A), SW47.1
unnamed: D48.2 (A), SW48.1
unnamed: D49.2 (A), SW49.1
unnamed: D50.2 (A), SW50.1
unnamed: D51.2 (A), SW51.1
unnamed: D52.2 (A), SW52.1
unnamed: D53.2 (A), SW53.1
unnamed: D54.2 (A), SW54.1
unnamed: D55.2 (A), SW55.1
unnamed: D56.2 (A), SW56.1
unnamed: D57.2 (A), SW57.1
unnamed: D58.1 (K), Q2.2 (S), U4.1 (VIN), U4.3 (EN)
unnamed: Q1.3 (D), SW29.3 (C)
unnamed: Q2.3 (D), SW58.1 (A)
